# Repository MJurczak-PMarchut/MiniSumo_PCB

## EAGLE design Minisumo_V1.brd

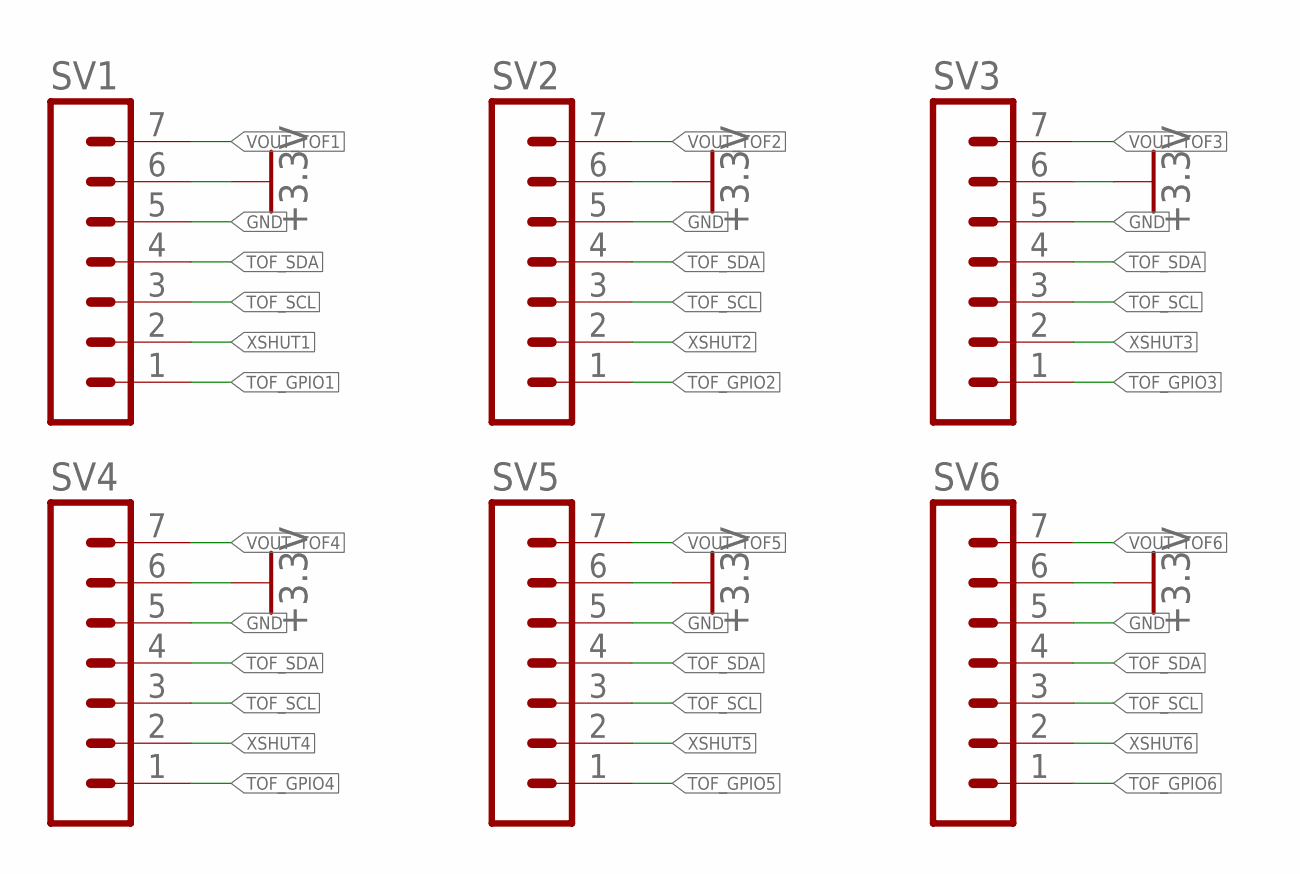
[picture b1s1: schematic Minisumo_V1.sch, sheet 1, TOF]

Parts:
SV1, SV2, SV3, SV4, SV5, SV6: MA07-1

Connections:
+3.3V: SV1.6, SV2.6, SV3.6, SV4.6, SV5.6, SV6.6; also elsewhere on the board
GND: SV1.5, SV2.5, SV3.5, SV4.5, SV5.5, SV6.5; also elsewhere on the board
TOF_GPIO1: SV1.1; also elsewhere on the board
TOF_GPIO2: SV2.1; also elsewhere on the board
TOF_GPIO3: SV3.1; also elsewhere on the board
TOF_GPIO4: SV4.1; also elsewhere on the board
TOF_GPIO5: SV5.1; also elsewhere on the board
TOF_GPIO6: SV6.1; also elsewhere on the board
TOF_SCL: SV1.3, SV2.3, SV3.3, SV4.3, SV5.3, SV6.3; also elsewhere on the board
TOF_SDA: SV1.4, SV2.4, SV3.4, SV4.4, SV5.4, SV6.4; also elsewhere on the board
VOUT_TOF1: SV1.7
VOUT_TOF2: SV2.7
VOUT_TOF3: SV3.7
VOUT_TOF4: SV4.7
VOUT_TOF5: SV5.7
VOUT_TOF6: SV6.7
XSHUT1: SV1.2; also elsewhere on the board
XSHUT2: SV2.2; also elsewhere on the board
XSHUT3: SV3.2; also elsewhere on the board
XSHUT4: SV4.2; also elsewhere on the board
XSHUT5: SV5.2; also elsewhere on the board
XSHUT6: SV6.2; also elsewhere on the board

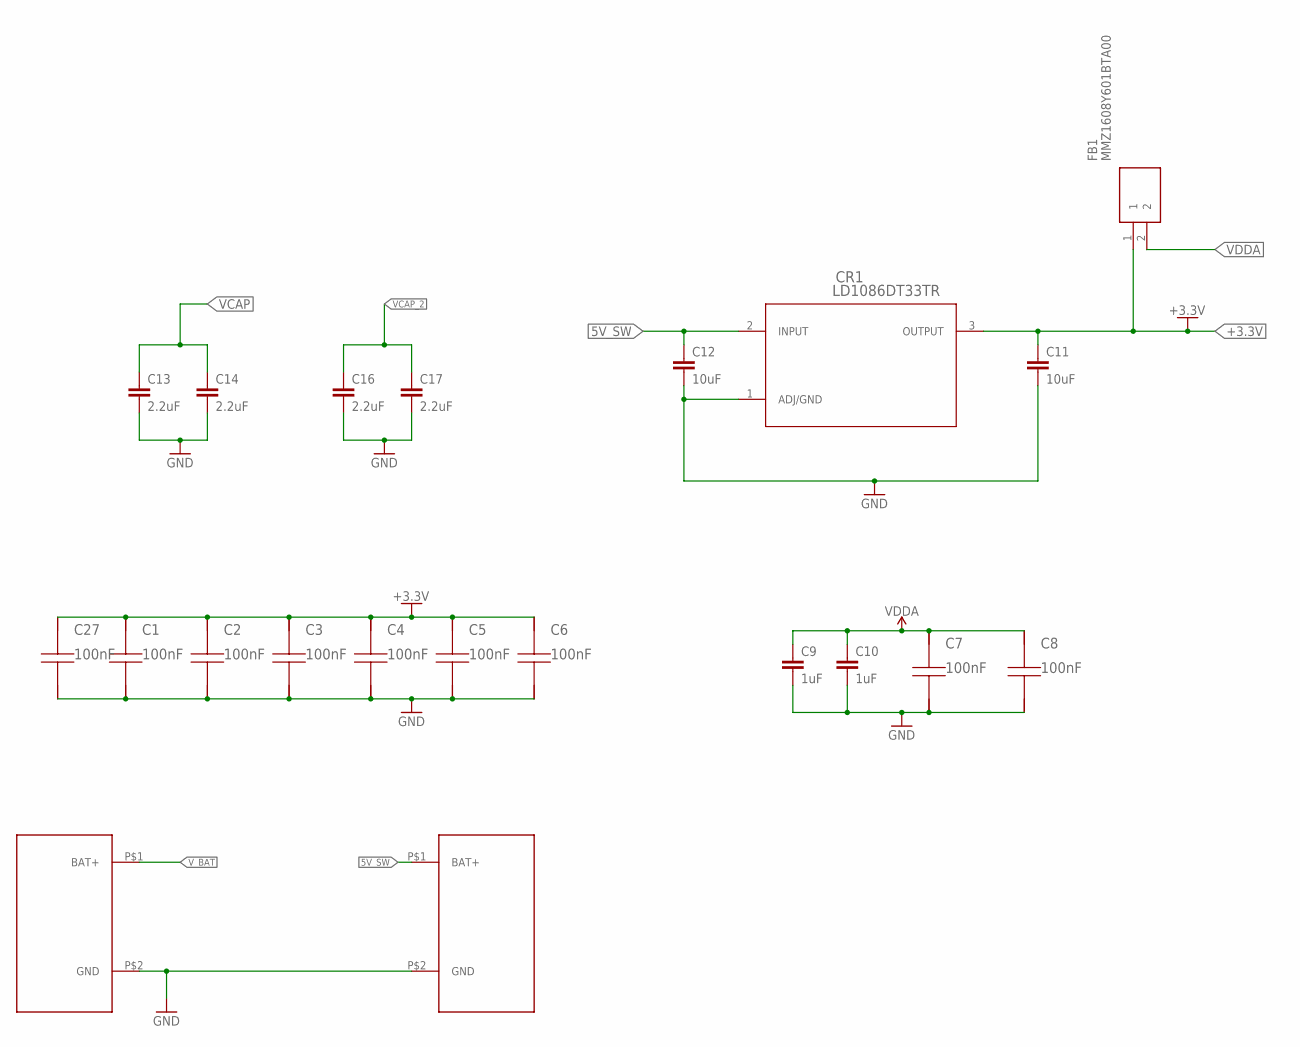
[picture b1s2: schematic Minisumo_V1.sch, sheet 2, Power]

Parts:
C1, C2, C3, C4, C5, C6, C7, C8, C27: 100nF; C0402
C9, C10: 1uF; C0402; MANUFACTURER_PART_NO EMK105BJ105KV-F
C11, C12: 10uF; C0603; MANUFACTURER_PART_NO GRM188R61E106KA73D
C13, C16: 2.2uF; C0603; MANUFACTURER_PART_NO EMK107BJ225KA-T
C14, C17: 2.2uF; C0603; MANUFACTURER_PART_NO GRM188R61E106KA73D
CR1: LD1086DT33TR; D2PAK_STM
FB1: MMZ1608Y601BTA00; BEADC1608X95N
U$6, U$7: BAT_POW

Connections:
5V_SW: C12.1, CR1.2 (INPUT), U$7.P$1 (BAT+); also elsewhere on the board
+3.3V: C1.1, C2.1, C3.1, C4.1, C5.1, C6.1, C11.1, C27.1, CR1.3 (OUTPUT), FB1.1; also elsewhere on the board
GND: C1.2, C2.2, C3.2, C4.2, C5.2, C6.2, C7.2, C8.2, C9.2, C10.2, C11.2, C12.2, C13.2, C14.2, C16.2, C17.2, C27.2, CR1.1 (ADJ/GND), U$6.P$2 (GND), U$7.P$2 (GND); also elsewhere on the board
VCAP: C13.1, C14.1; also elsewhere on the board
VCAP_2: C16.1, C17.1; also elsewhere on the board
VDDA: C7.1, C8.1, C9.1, C10.1, FB1.2; also elsewhere on the board
V_BAT: U$6.P$1 (BAT+); also elsewhere on the board

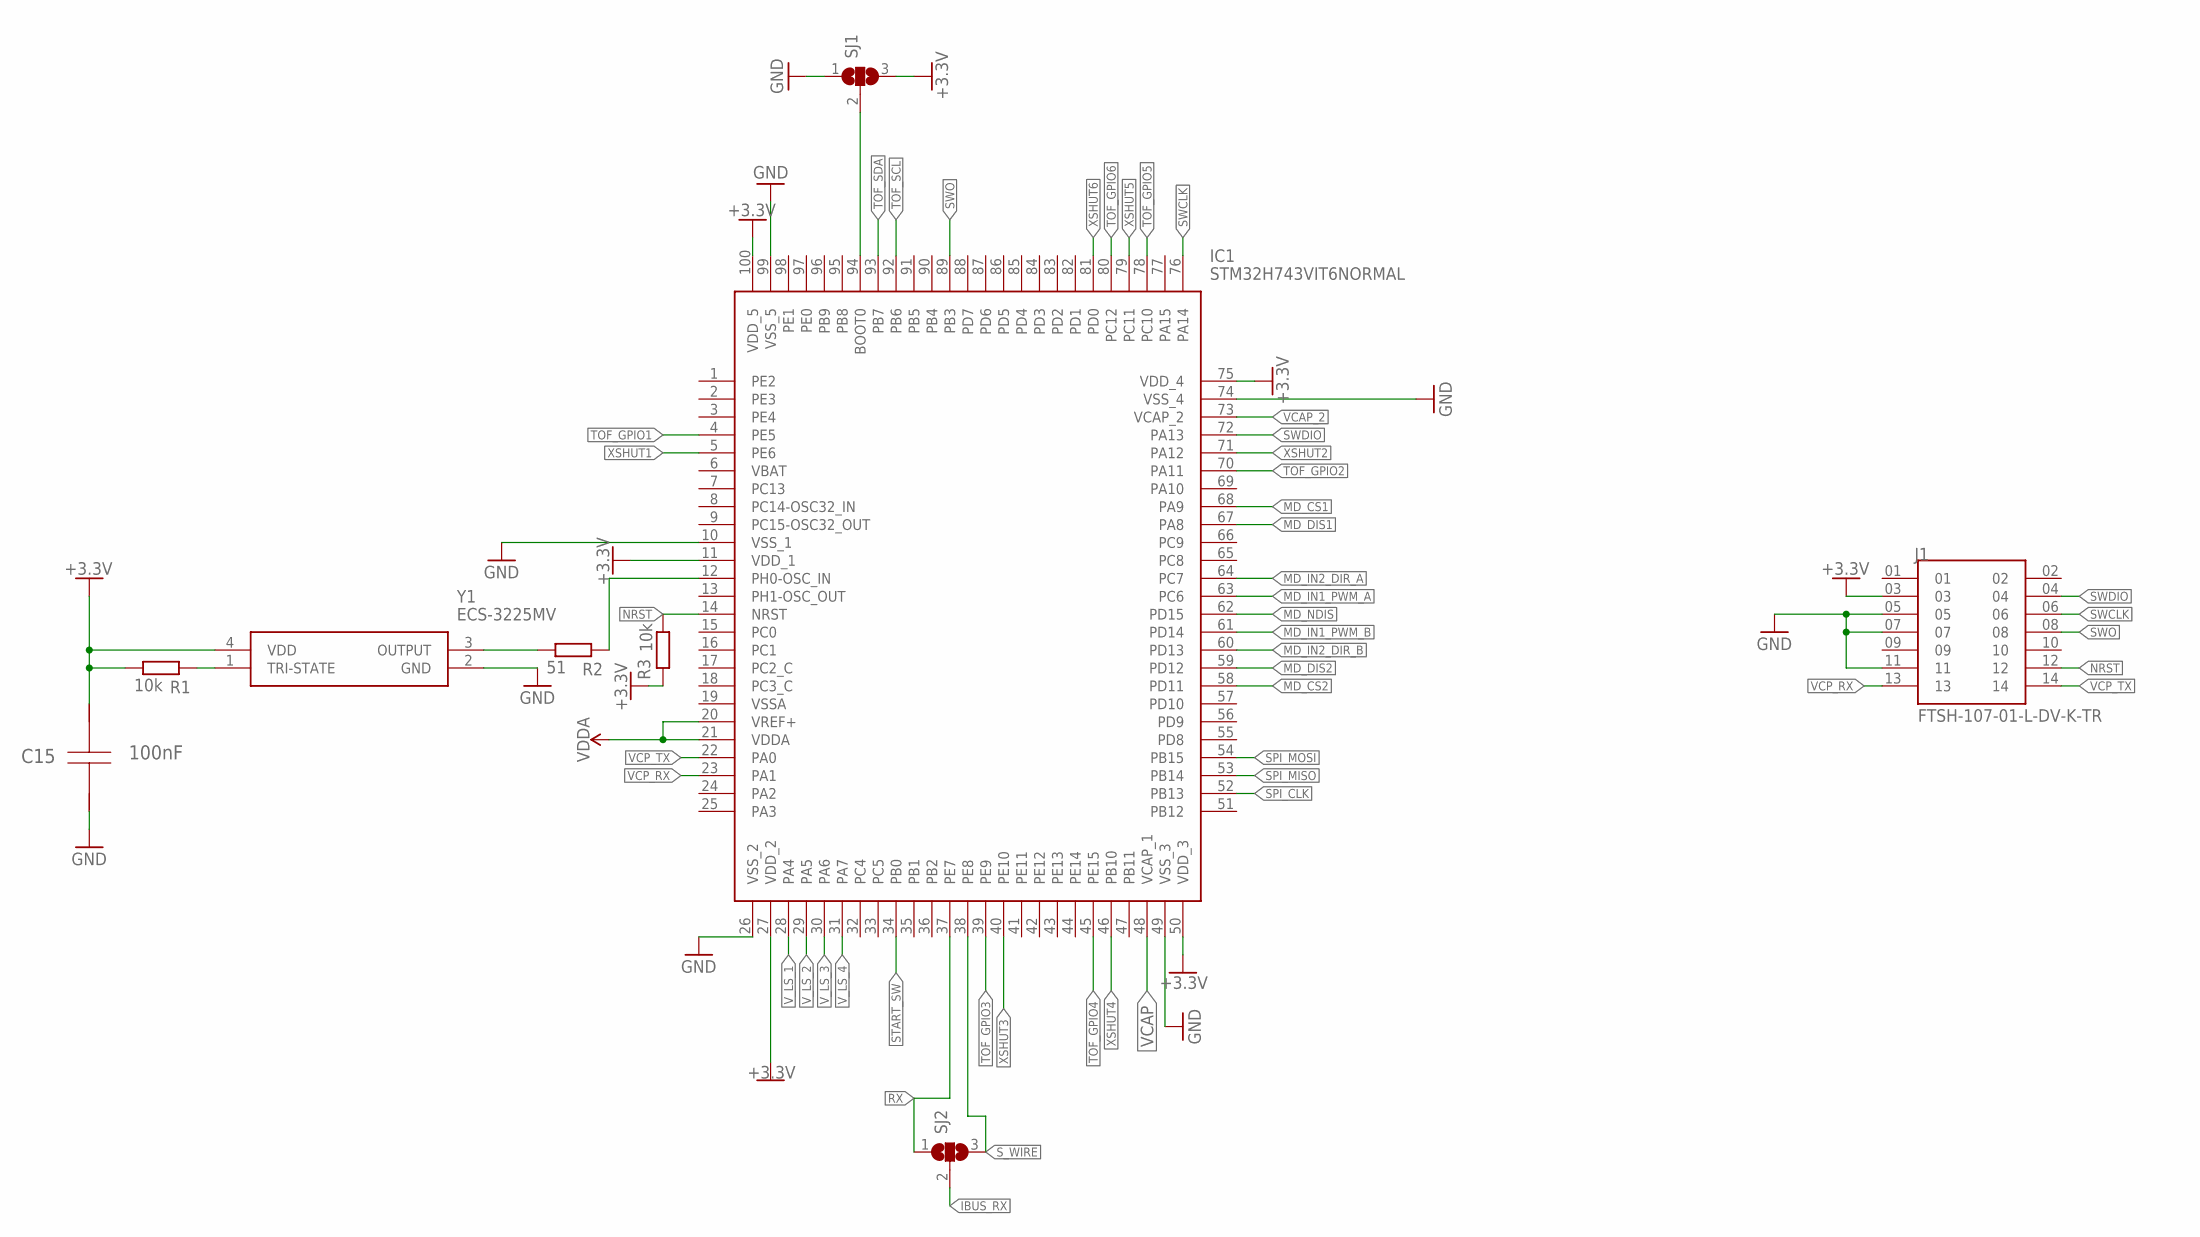
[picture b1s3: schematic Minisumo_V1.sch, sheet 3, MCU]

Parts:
C15: 100nF; C0402
IC1: STM32H743VIT6NORMAL; QFP50P1600X1600X160-100N
J1: FTSH-107-01-L-DV-K-TR; SAMTEC_FTSH-107-01-L-DV-K-TR
R1, R3: 10k; R0402
R2: 51; R0402
SJ1, SJ2: SJ2W; SJ_2
Y1: ECS-3225MV; ECS3225MV

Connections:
+3.3V: C15.1, IC1.11 (VDD_1), IC1.27 (VDD_2), IC1.50 (VDD_3), IC1.75 (VDD_4), IC1.100 (VDD_5), J1.03, R1.1, R3.2, SJ1.3, Y1.4 (VDD); also elsewhere on the board
GND: C15.2, IC1.10 (VSS_1), IC1.26 (VSS_2), IC1.49 (VSS_3), IC1.74 (VSS_4), IC1.99 (VSS_5), J1.05, J1.07, J1.11, SJ1.1, Y1.2 (GND); also elsewhere on the board
IBUS_RX: SJ2.2; also elsewhere on the board
MD_CS1: IC1.68 (PA9); also elsewhere on the board
MD_CS2: IC1.58 (PD11); also elsewhere on the board
MD_DIS1: IC1.67 (PA8); also elsewhere on the board
MD_DIS2: IC1.59 (PD12); also elsewhere on the board
MD_IN1_PWM_A: IC1.63 (PC6); also elsewhere on the board
MD_IN1_PWM_B: IC1.61 (PD14); also elsewhere on the board
MD_IN2_DIR_A: IC1.64 (PC7); also elsewhere on the board
MD_IN2_DIR_B: IC1.60 (PD13); also elsewhere on the board
MD_NDIS: IC1.62 (PD15); also elsewhere on the board
unnamed: IC1.94 (BOOT0), SJ1.2
unnamed: R2.1, Y1.3 (OUTPUT)
unnamed: R1.2, Y1.1 (TRI-STATE)
unnamed: IC1.12 (PH0-OSC_IN), R2.2
NRST: IC1.14 (NRST), J1.12, R3.1
RX: IC1.37 (PE7), SJ2.1
SPI_CLK: IC1.52 (PB13); also elsewhere on the board
SPI_MISO: IC1.53 (PB14); also elsewhere on the board
SPI_MOSI: IC1.54 (PB15); also elsewhere on the board
START_SW: IC1.34 (PB0); also elsewhere on the board
SWCLK: IC1.76 (PA14), J1.06
SWDIO: IC1.72 (PA13), J1.04
SWO: IC1.89 (PB3), J1.08
S_WIRE: IC1.38 (PE8), SJ2.3
TOF_GPIO1: IC1.4 (PE5); also elsewhere on the board
TOF_GPIO2: IC1.70 (PA11); also elsewhere on the board
TOF_GPIO3: IC1.39 (PE9); also elsewhere on the board
TOF_GPIO4: IC1.45 (PE15); also elsewhere on the board
TOF_GPIO5: IC1.78 (PC10); also elsewhere on the board
TOF_GPIO6: IC1.80 (PC12); also elsewhere on the board
TOF_SCL: IC1.92 (PB6); also elsewhere on the board
TOF_SDA: IC1.93 (PB7); also elsewhere on the board
VCAP: IC1.48 (VCAP_1); also elsewhere on the board
VCAP_2: IC1.73 (VCAP_2); also elsewhere on the board
VCP_RX: IC1.23 (PA1), J1.13
VCP_TX: IC1.22 (PA0), J1.14
VDDA: IC1.20 (VREF+), IC1.21 (VDDA); also elsewhere on the board
V_LS_1: IC1.28 (PA4); also elsewhere on the board
V_LS_2: IC1.29 (PA5); also elsewhere on the board
V_LS_3: IC1.30 (PA6); also elsewhere on the board
V_LS_4: IC1.31 (PA7); also elsewhere on the board
XSHUT1: IC1.5 (PE6); also elsewhere on the board
XSHUT2: IC1.71 (PA12); also elsewhere on the board
XSHUT3: IC1.40 (PE10); also elsewhere on the board
XSHUT4: IC1.46 (PB10); also elsewhere on the board
XSHUT5: IC1.79 (PC11); also elsewhere on the board
XSHUT6: IC1.81 (PD0); also elsewhere on the board

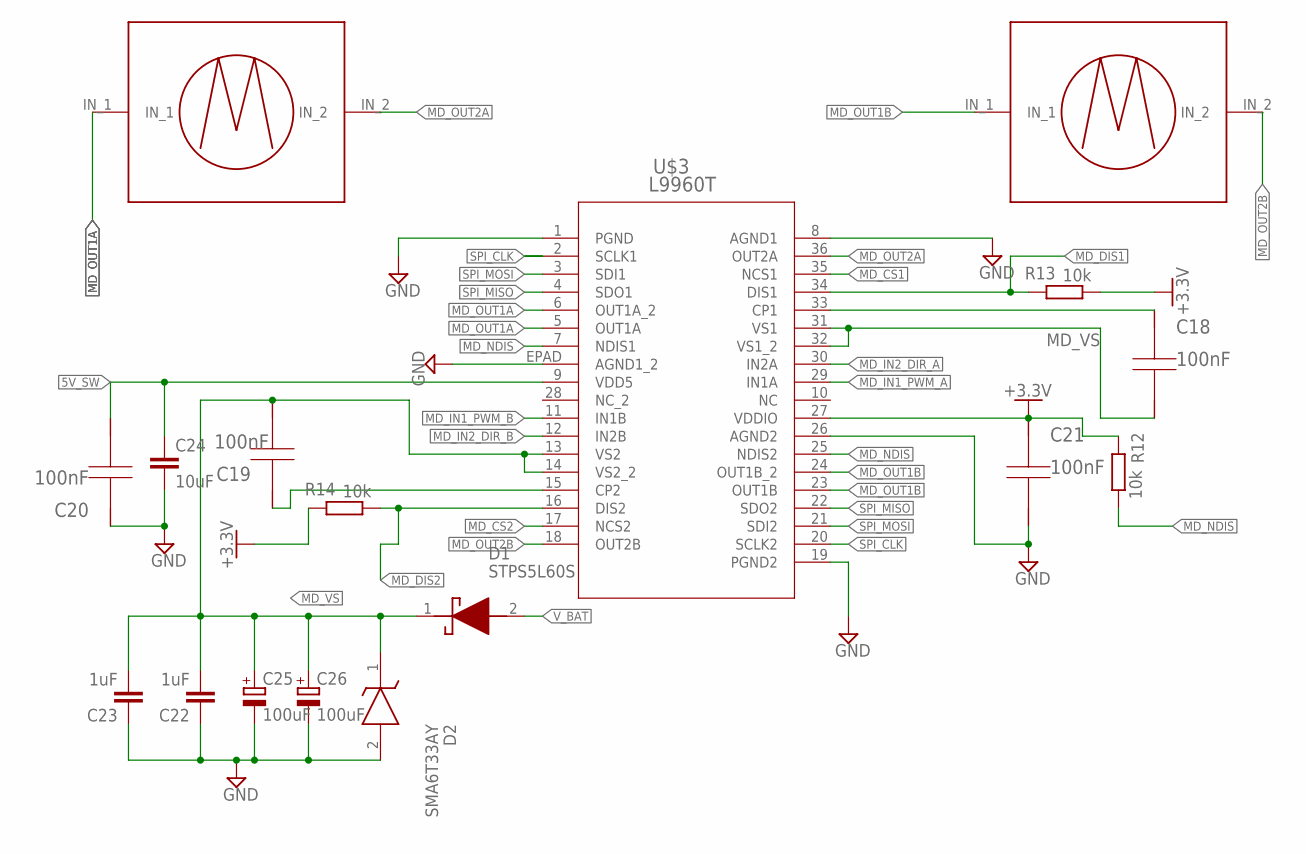
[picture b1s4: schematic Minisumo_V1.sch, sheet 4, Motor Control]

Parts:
C18, C19, C20, C21: 100nF; C0402
C22, C23: 1uF; C0402; MANUFACTURER_PART_NO EMK105BJ105KV-F
C24: 10uF; C1210; MANUFACTURER_PART_NO UMK325AB7106KMHP
C25, C26: 100uF; UD-8X10_NICHICON; MANUFACTURER_PART_NO RVT1H101M0810
D1: STPS5L60S; DIOM8059X265N
D2: SMA6T33AY; DIOM5126X265N
R12, R13, R14: 10k; R0402
U$3: L9960T; POWERSSO-36_STM
U$4, U$5: MD_OUT

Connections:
5V_SW: C20.2, C24.1, U$3.9 (VDD5); also elsewhere on the board
+3.3V: C21.1, R12.2, R13.1, R14.2, U$3.27 (VDDIO); also elsewhere on the board
GND: C20.1, C21.2, C22.1, C23.1, C24.2, C25.-, C26.-, D2.2 (A), U$3.1 (PGND), U$3.8 (AGND1), U$3.19 (PGND2), U$3.26 (AGND2), U$3.EPAD (AGND1_2); also elsewhere on the board
MD_CS1: U$3.35 (NCS1); also elsewhere on the board
MD_CS2: U$3.17 (NCS2); also elsewhere on the board
MD_DIS1: R13.2, U$3.34 (DIS1); also elsewhere on the board
MD_DIS2: R14.1, U$3.16 (DIS2); also elsewhere on the board
MD_IN1_PWM_A: U$3.29 (IN1A); also elsewhere on the board
MD_IN1_PWM_B: U$3.11 (IN1B); also elsewhere on the board
MD_IN2_DIR_A: U$3.30 (IN2A); also elsewhere on the board
MD_IN2_DIR_B: U$3.12 (IN2B); also elsewhere on the board
MD_NDIS: R12.1, U$3.7 (NDIS1), U$3.25 (NDIS2); also elsewhere on the board
MD_OUT1A: U$3.5 (OUT1A), U$3.6 (OUT1A_2), U$4.IN_1
MD_OUT1B: U$3.23 (OUT1B), U$3.24 (OUT1B_2), U$5.IN_1
MD_OUT2A: U$3.36 (OUT2A), U$4.IN_2
MD_OUT2B: U$3.18 (OUT2B), U$5.IN_2
MD_VS: C18.2, C19.2, C22.2, C23.2, C25.+, C26.+, D1.1 (K), D2.1 (K), U$3.13 (VS2), U$3.14 (VS2_2), U$3.31 (VS1), U$3.32 (VS1_2)
unnamed: C18.1, U$3.33 (CP1)
unnamed: C19.1, U$3.15 (CP2)
SPI_CLK: U$3.2 (SCLK1), U$3.20 (SCLK2); also elsewhere on the board
SPI_MISO: U$3.4 (SDO1), U$3.22 (SDO2); also elsewhere on the board
SPI_MOSI: U$3.3 (SDI1), U$3.21 (SDI2); also elsewhere on the board
V_BAT: D1.2 (A); also elsewhere on the board

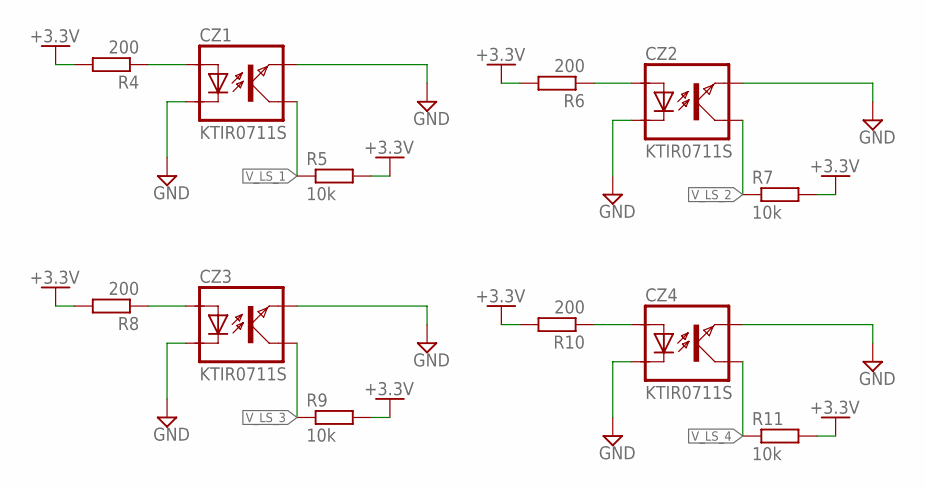
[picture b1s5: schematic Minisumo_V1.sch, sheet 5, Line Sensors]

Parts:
CZ1, CZ2, CZ3, CZ4: KTIR0711S; TOP; MANUFACTURER_PART_NO ITR8307/S18/TR8(B)
R4, R6, R8, R10: 200; R0402
R5, R7, R9, R11: 10k; R0402

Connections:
+3.3V: R4.2, R5.2, R6.2, R7.2, R8.2, R9.2, R10.2, R11.2; also elsewhere on the board
GND: CZ1.EMITER, CZ1.KATODA, CZ2.EMITER, CZ2.KATODA, CZ3.EMITER, CZ3.KATODA, CZ4.EMITER, CZ4.KATODA; also elsewhere on the board
unnamed: CZ1.ANODA, R4.1
unnamed: CZ2.ANODA, R6.1
unnamed: CZ3.ANODA, R8.1
unnamed: CZ4.ANODA, R10.1
V_LS_1: CZ1.KOLEKTOR, R5.1; also elsewhere on the board
V_LS_2: CZ2.KOLEKTOR, R7.1; also elsewhere on the board
V_LS_3: CZ3.KOLEKTOR, R9.1; also elsewhere on the board
V_LS_4: CZ4.KOLEKTOR, R11.1; also elsewhere on the board

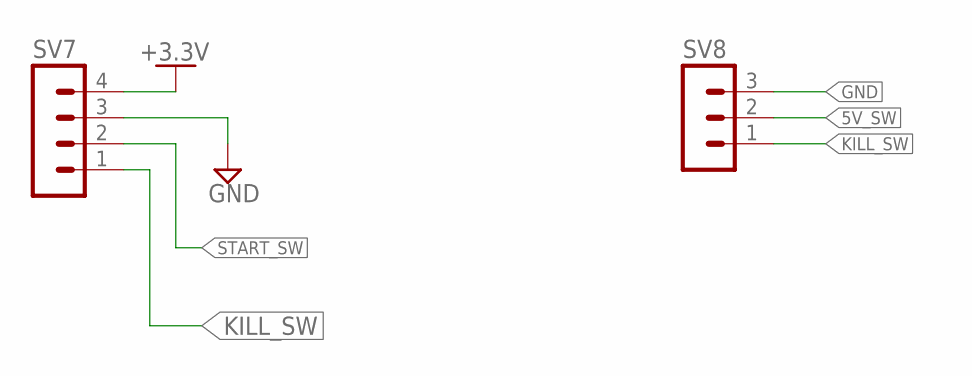
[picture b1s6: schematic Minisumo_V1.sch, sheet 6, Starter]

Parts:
SV7: MA04-1
SV8: MA03-1

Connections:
5V_SW: SV8.2; also elsewhere on the board
+3.3V: SV7.4; also elsewhere on the board
GND: SV7.3, SV8.3; also elsewhere on the board
KILL_SW: SV7.1, SV8.1
START_SW: SV7.2; also elsewhere on the board

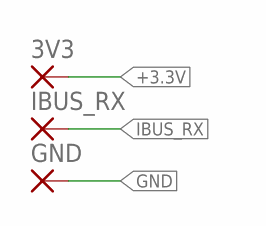
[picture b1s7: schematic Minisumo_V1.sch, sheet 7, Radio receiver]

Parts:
3V3: SMD2; SMD1,27-2,54
GND: SMD2; SMD1,27-2,54
IBUS_RX: SMD2; SMD1,27-2,54

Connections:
+3.3V: 3V3.1; also elsewhere on the board
GND: GND.1; also elsewhere on the board
IBUS_RX: IBUS_RX.1; also elsewhere on the board

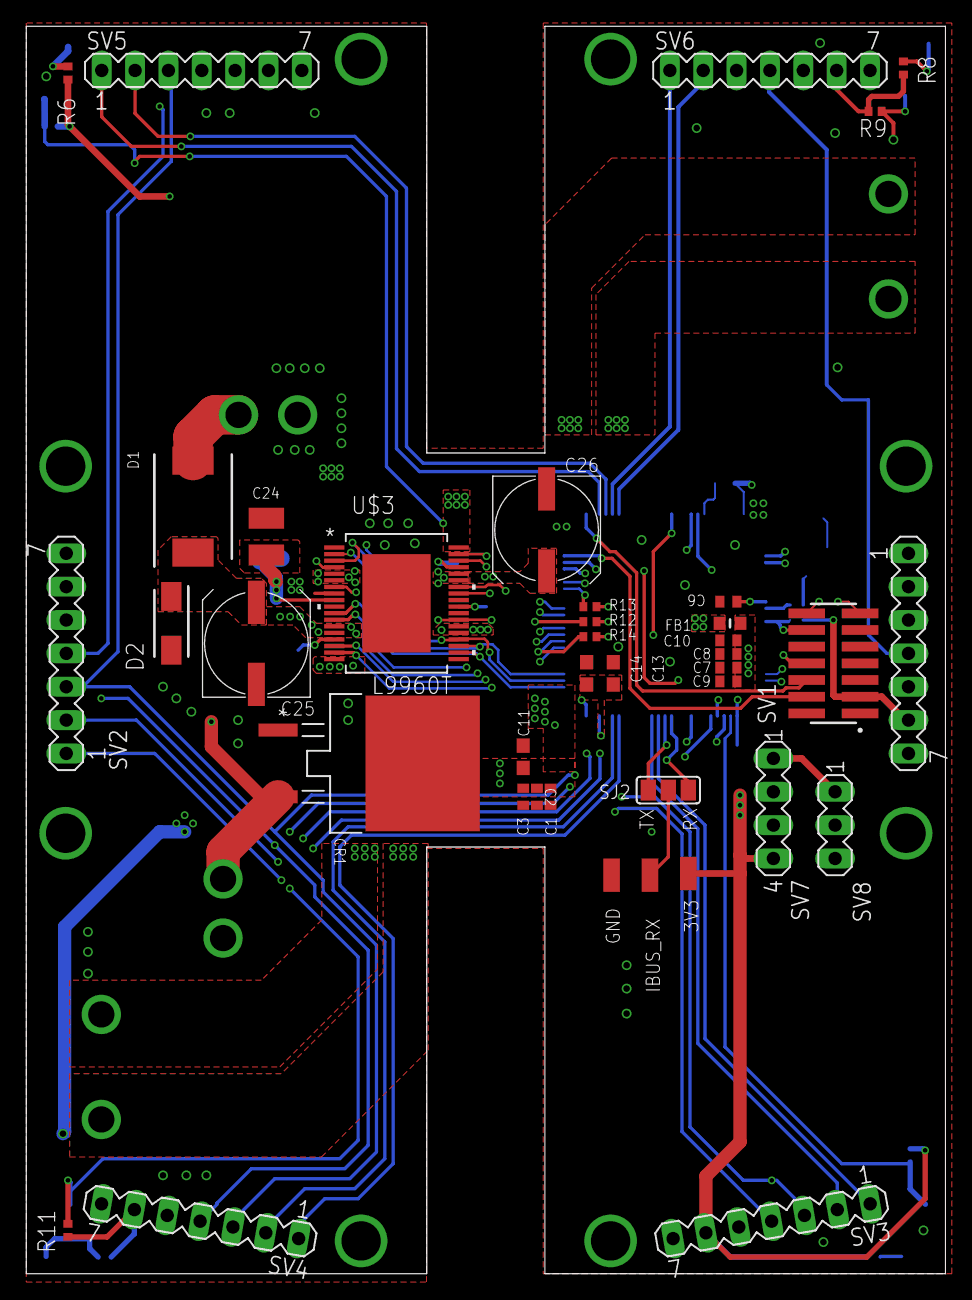
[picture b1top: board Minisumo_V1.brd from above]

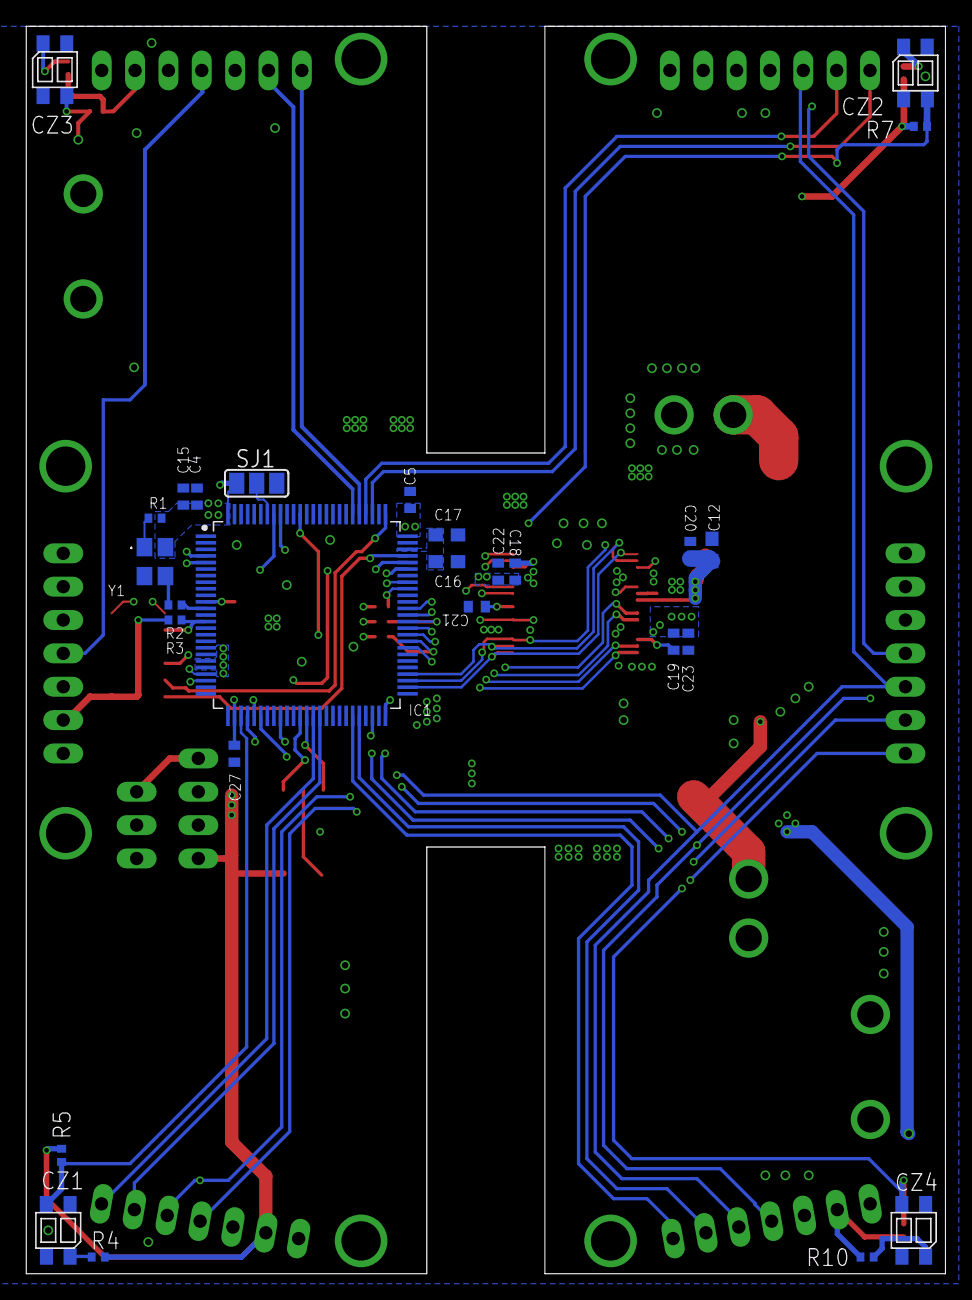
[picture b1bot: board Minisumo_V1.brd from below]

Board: 4 copper layers, 70.0 x 95.0 mm, 70 parts (27 on the bottom side), 63 nets.

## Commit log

2021-11-06 Add parts
2021-11-07 07_11_2021_15_50
2021-11-07 07_11_2021_22_21
2021-11-07 07_11_2021_23_28
2021-11-09 final
2023-02-01 remp

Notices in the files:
parts and their libraries:
COPYRIGHT: Copyright (C) 2021 Ultra Librarian. All rights reserved.
SparkFun-PowerSymbols: Licensing: Creative Commons ShareAlike 4.0 International - https://creativecommons.org/licenses/by-sa/4.0
